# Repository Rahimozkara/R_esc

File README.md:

AM32 Single ESC
⚠️ Disclaimer & Project Status: This is an educational project designed by an engineering student. Please note that the current hardware revision has not yet been physically tested. Manufacture, flash, and use at your own risk.

📖 About the Project
This is an open-source, high-performance single Electronic Speed Controller (ESC) designed for FPV drones and custom robotics. It is fully compatible with the AM32 firmware, providing smooth and efficient brushless DC (BLDC) motor control.

✨ Features
Firmware: AM32 Open Source Firmware

Microcontroller: STM32F051

Estimated Continuous Current: ~20A

Supported Protocols: DShot300 / DShot600 / PWM

Application: FPV Drones & Custom Robotics

🛠️ Hardware Design & Known Issues
The schematic and PCB layout for this project were designed using KiCad. The board layout is optimized for efficient power delivery and stable thermal dissipation.

🛑 Important Hardware Note (Current Sensing):
In the current schematic, an INA199A1DCKR current sense amplifier is used, which features a gain of 50 V/V. However, the default AM32 firmware code expects a current sensor with a gain of 65 V/V.

Recommendation: To ensure accurate current readings, you must either adjust the multiplier in the AM32 firmware code to account for the 50x gain, or replace this IC with a 65x gain variant in future PCB revisions.

🚀 How to Manufacture
All necessary hardware files for manufacturing are included in this repository. You can directly use the provided Gerber files for PCB fabrication.

💻 Flashing & Setup
Initial firmware flashing can be done via the SWD pads located on the board using an ST-Link. Once the bootloader is installed, further firmware updates and configuration can be easily managed via Betaflight passthrough.

📄 License
This project is open-source. Feel free to use, modify, and contribute!

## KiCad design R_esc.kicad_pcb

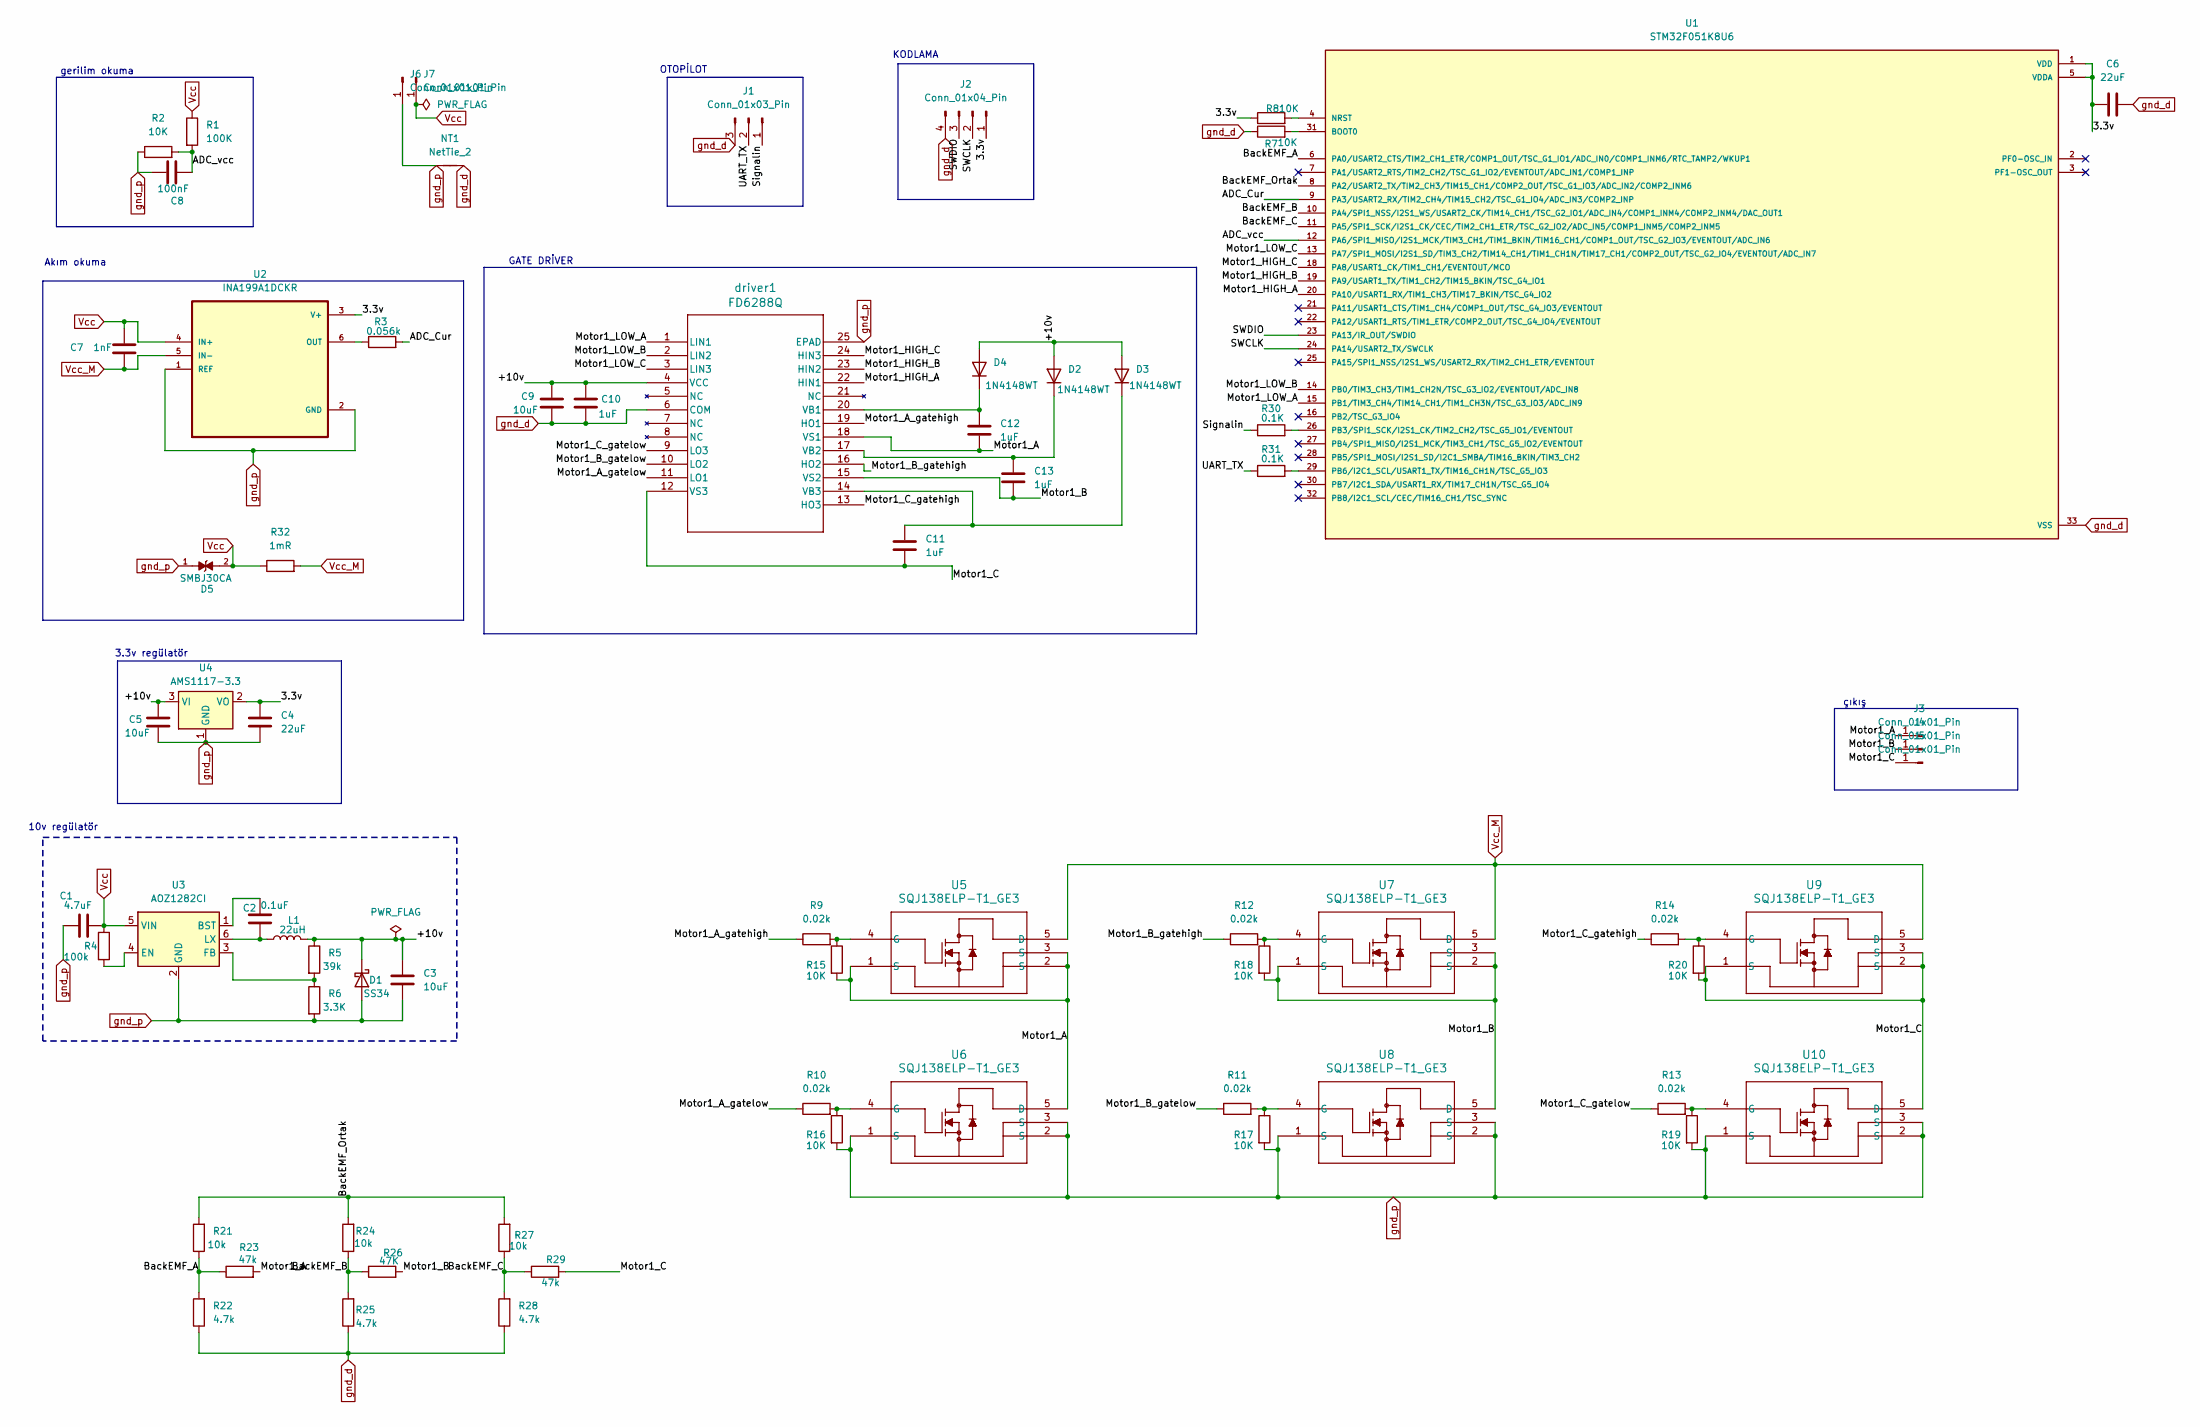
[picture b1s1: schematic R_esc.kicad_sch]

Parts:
C1: 4.7uF; C_0805_2012Metric
C2: 0.1uF; C_0603_1608Metric
C3, C5, C9: 10uF; C_1206_3216Metric
C4, C6: 22uF; C_1206_3216Metric
C7: 1nF; C_0603_1608Metric
C8: 100nF; C_0603_1608Metric
C10, C11, C12, C13: 1uF; C_0805_2012Metric
D1: SS34; D_SMA
D2, D3, D4: 1N4148WT; D_SOD-523
D5: SMBJ30CA; DIOM4336X265N; PARTREV I2102
J1: Conn_01x03_Pin; PinHeader_1x03_P2.54mm_Vertical
J2: Conn_01x04_Pin; PinHeader_1x04_P2.54mm_Vertical
J3, J4, J5, J6, J7: Conn_01x01_Pin; PinHeader_1x01_P2.54mm_Vertical
L1: 22uH; L_6.3x6.3_H3
NT1: NetTie_2; NetTie-2_SMD_Pad0.5mm
R1: 100K; R_0603_1608Metric
R2, R7, R8, R15, R16, R17, R18, R19, R20: 10K; R_0603_1608Metric
R3: 0.056k; R_0603_1608Metric
R4: 100k; R_0603_1608Metric
R5: 39k; R_0603_1608Metric
R6: 3.3K; R_0603_1608Metric
R9, R10, R11, R12, R13, R14: 0.02k; R_0603_1608Metric
R21, R24, R27: 10k; R_0603_1608Metric
R22, R25, R28: 4.7k; R_0603_1608Metric
R23, R29: 47k; R_0603_1608Metric
R26: 47K; R_0603_1608Metric
R30, R31: 0.1K; R_0603_1608Metric
R32: 1mR; R_2512_6332Metric
U1: STM32F051K8U6; QFN50P500X500X60-33N; PARTREV 7
U2: INA199A1DCKR; SOT65P210X110-6N
U3: AOZ1282CI; SOT-23-6
U4: AMS1117-3.3; SOT-223-3_TabPin2
U5, U6, U7, U8, U9, U10: SQJ138ELP-T1_GE3; PowerPAK_SO-8L_3_VIS
driver1: FD6288Q; QFN24_FOR-M

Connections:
/+10v: C3.1, C5.1, C9.1, C10.1, D1.1 (K), D2.2 (A), D3.2 (A), D4.2 (A), L1.2, R5.1, U4.3 (VI), driver1.4 (VCC)
/ADC_Cur: R3.2, U1.9 (PA3/USART2_RX/TIM2_CH4/TIM15_CH2/TSC_G1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)
/ADC_vcc: C8.2, R1.2, R2.2, U1.12 (PA6/SPI1_MISO/I2S1_MCK/TIM3_CH1/TIM1_BK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)
/BackEMF_A: R21.1, R22.2, R23.1, U1.6 (PA0/USART2_CTS/TIM2_CH1_ETR/COMP1_OUT/T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)
/BackEMF_B: R24.1, R25.2, R26.1, U1.10 (PA4/SPI1_NSS/I2S1_WS/USART2_CK/TIM14_CH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)
/BackEMF_C: R27.1, R28.2, R29.1, U1.11 (PA5/SPI1_SCK/I2S1_CK/CEC/TIM2_CH1_ETR/T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)
/BackEMF_Ortak: R21.2, R24.2, R27.2, U1.8 (PA2/USART2_TX/TIM2_CH3/TIM15_CH1/COMP2_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)
/Motor1_A: C12.2, J3.1, R15.2, R23.2, U5.1 (S), U5.2 (S), U5.3 (S), U6.5 (D), driver1.18 (VS1)
/Motor1_A_gatehigh: R9.1, driver1.19 (HO1)
/Motor1_A_gatelow: R10.1, driver1.11 (LO1)
/Motor1_B: C13.2, J4.1, R18.2, R26.2, U7.1 (S), U7.2 (S), U7.3 (S), U8.5 (D), driver1.15 (VS2)
/Motor1_B_gatehigh: R12.1, driver1.16 (HO2)
/Motor1_B_gatelow: R11.1, driver1.10 (LO2)
/Motor1_C: C11.2, J5.1, R20.2, R29.2, U9.1 (S), U9.2 (S), U9.3 (S), U10.5 (D), driver1.12 (VS3)
/Motor1_C_gatehigh: R14.1, driver1.13 (HO3)
/Motor1_C_gatelow: R13.1, driver1.9 (LO3)
/Motor1_HIGH_A: U1.20 (PA10/USART1_RX/TIM1_CH3/TIM17_BKIN/TSC_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), driver1.22 (HIN1)
/Motor1_HIGH_B: U1.19 (PA9/USART1_TX/TIM1_CH2/TIM15_BKIN/TSC_G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), driver1.23 (HIN2)
/Motor1_HIGH_C: U1.18 (PA8/USART1_CK/TIM1_CH1/EVENTOUT/MCO), driver1.24 (HIN3)
/Motor1_LOW_A: U1.15 (PB1/TIM3_CH4/TIM14_CH1/TIM1_CH3N/TSC_G3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), driver1.1 (LIN1)
/Motor1_LOW_B: U1.14 (PB0/TIM3_CH3/TIM1_CH2N/TSC_G3_IO2/EVENT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), driver1.2 (LIN2)
/Motor1_LOW_C: U1.13 (PA7/SPI1_MOSI/I2S1_SD/TIM3_CH2/TIM14_CH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), driver1.3 (LIN3)
/SWCLK: J2.2, U1.24 (PA14/USART2_TX/SWCLK)
/SWDIO: J2.3, U1.23 (PA13/IR_OUT/SWDIO)
/Signalin: J1.1, R30.1
/UART_TX: J1.2, R31.1
unnamed: C13.1, D2.1 (K), driver1.17 (VB2)
unnamed: C11.1, D3.1 (K), driver1.14 (VB3)
unnamed: C12.1, D4.1 (K), driver1.20 (VB1)
unnamed: R7.2, U1.31 (BOOT0)
unnamed: R8.2, U1.4 (NRST)
unnamed: R30.2, U1.26 (PB3/SPI1_SCK/I2S1_CK/TIM2_CH2/TSC_G5_IO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)
unnamed: R31.2, U1.29 (PB6/I2C1_SCL/USART1_TX/TIM16_CH1N/TSC_G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)
unnamed: R3.1, U2.6 (OUT)
unnamed: C2.1, U3.1 (BST)
unnamed: R4.2, U3.4 (EN)
unnamed: R5.2, R6.1, U3.3 (FB)
unnamed: C2.2, L1.1, U3.6 (LX)
unnamed: R9.2, R15.1, U5.4 (G)
unnamed: R10.2, R16.1, U6.4 (G)
unnamed: R12.2, R18.1, U7.4 (G)
unnamed: R11.2, R17.1, U8.4 (G)
unnamed: R14.2, R20.1, U9.4 (G)
unnamed: R13.2, R19.1, U10.4 (G)
VDD: C4.1, C6.2, J2.1, R8.1, U1.1 (VDD), U1.5 (VDDA), U1.17 (VDD), U2.3 (V+), U4.2 (VO)
Vcc: C1.1, C7.2, D5.2, J7.1, R1.1, R4.1, R32.1, U2.4 (IN+), U3.5 (VIN)
Vcc_M: C7.1, R32.2, U2.5 (IN-), U5.5 (D), U7.5 (D), U9.5 (D)
gnd_d: C6.1, C9.2, C10.2, J1.3, J2.4, NT1.2, R7.1, R22.1, R25.1, R28.1, U1.33 (VSS), driver1.6 (COM)
gnd_p: C1.2, C3.2, C4.2, C5.2, C8.1, D1.2 (A), D5.1, J6.1, NT1.1, R2.1, R6.2, R16.2, R17.2, R19.2, U2.1 (REF), U2.2 (GND), U3.2 (GND), U4.1 (GND), U6.1 (S), U6.2 (S), U6.3 (S), U8.1 (S), U8.2 (S), U8.3 (S), U10.1 (S), U10.2 (S), U10.3 (S), driver1.25 (EPAD)

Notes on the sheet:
3.3v regülatör
10v regülatör
KODLAMA
GATE DRİVER
çıkış
gerilim okuma
Akım okuma
OTOPİLOT

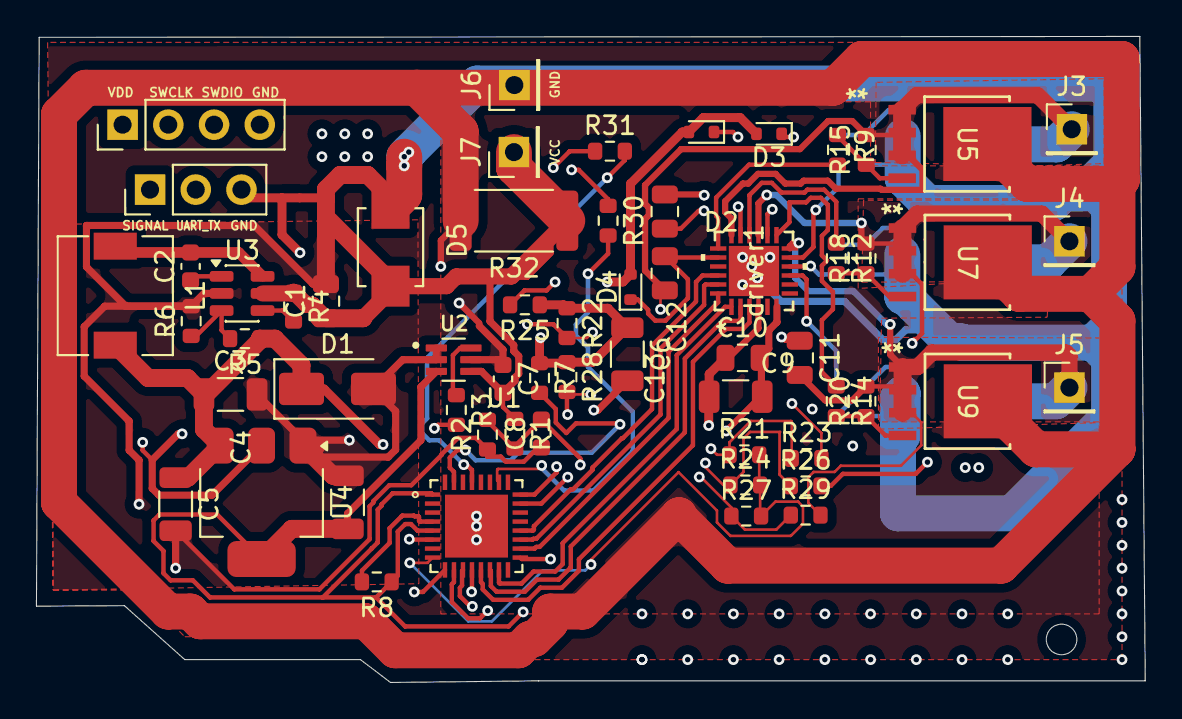
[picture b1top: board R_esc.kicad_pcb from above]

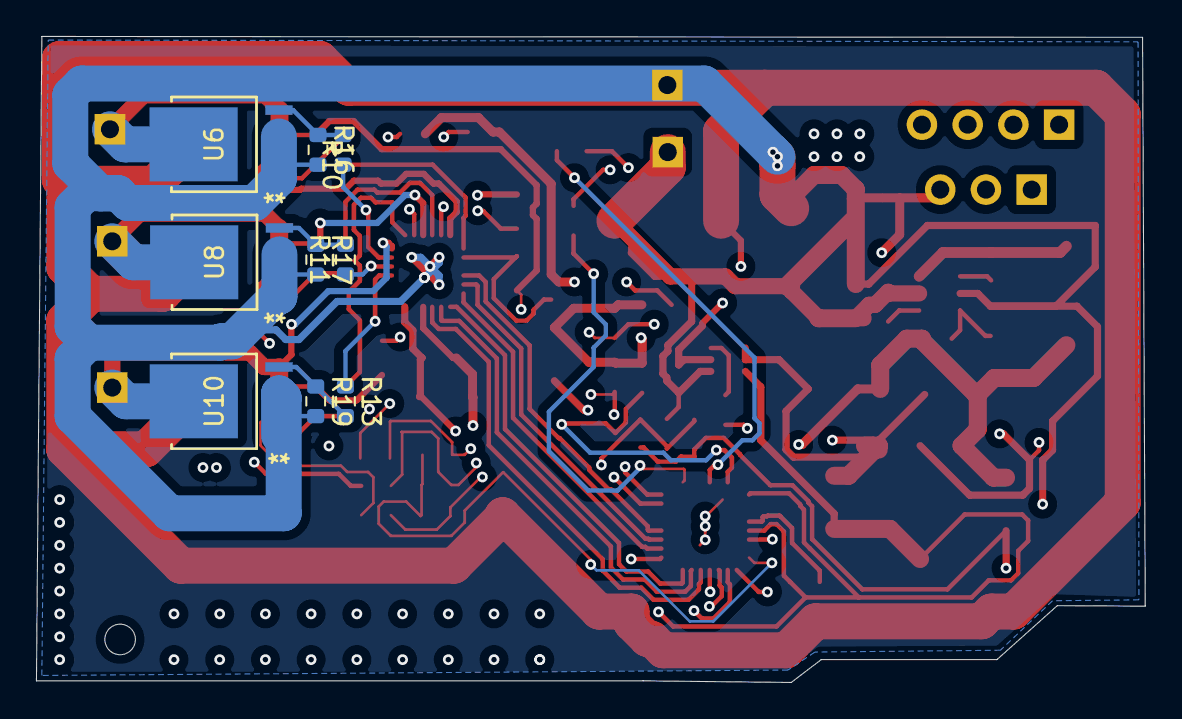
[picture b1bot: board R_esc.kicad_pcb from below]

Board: 4 copper layers, 61.6 x 35.9 mm, 70 parts (9 on the bottom side), 49 nets.

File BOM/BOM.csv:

Reference(s);Quantity;Value / Name;Footprint;Type
U1;1;STM32F051K8U6;QFN50P500X500X60-33N;Microcontroller
driver1;1;FD6288Q;QFN24_FOR-M;Gate Driver
U5, U6, U7, U8, U9, U10;6;SQJ138ELP-T1_GE3;PowerPAK_SO-8L_3_VIS;N-Channel MOSFET
U2;1;INA199A1DCKR;SOT65P210X110-6N;Current Sense Amplifier (Gain: 50)
U3;1;AOZ1282CI;SOT-23-6;Voltage Regulator (Buck)
U4;1;AMS1117-3.3;SOT-223-3_TabPin2;LDO Regulator (3.3V)
D1;"1,""SS34""";D_SMA;Schottky Diode;
D2, D3, D4;3;1N4148WT;D_SOD-523;Signal Diode
D5;"1,""SMBJ30CA""";DIOM4336X265N;TVS Diode;
C4, C6;2;22uF;C_1206_3216Metric;Capacitor
C3, C5, C9;3;10uF;C_1206_3216Metric;Capacitor
C1;1;4.7uF;C_0805_2012Metric;Capacitor
C10, C11, C12, C13;4;1uF;C_0805_2012Metric;Capacitor
C8;1;100nF;C_0603_1608Metric;Capacitor
C2;1;0.1uF;C_0603_1608Metric;Capacitor
C7;1;1nF;C_0603_1608Metric;Capacitor
R1, R4;2;100K;R_0603_1608Metric;Resistor
R23, R26, R29;3;47k;R_0603_1608Metric;Resistor
R5;1;39k;R_0603_1608Metric;Resistor
R2, R7, R8, R15, R16, R17, R18, R19, R20, R21, R24, R27;12;10K;R_0603_1608Metric;Resistor
R22, R25, R28;3;4.7k;R_0603_1608Metric;Resistor
R6;1;3.3K;R_0603_1608Metric;Resistor
R30, R31;2;0.1K;R_0603_1608Metric;Resistor
R3;1;0.056k;R_0603_1608Metric;Resistor
R9, R10, R11, R12, R13, R14;6;0.02k;R_0603_1608Metric;Resistor (Gate)
R32;1;1mR;R_2512_6332Metric;Shunt Resistor
L1;1;22uH;L_6.3x6.3_H3;Inductor
J2;1;Conn_01x04_Pin;PinHeader_1x04_P2.54mm_Vertical;Connector
J1;1;Conn_01x03_Pin;PinHeader_1x03_P2.54mm_Vertical;Connector
J3, J4, J5, J6, J7;5;Conn_01x01_Pin;PinHeader_1x01_P2.54mm_Vertical;Connector (Single Pin)
NT1;1;NetTie_2;NetTie-2_SMD_Pad0.5mm;Net Tie

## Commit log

2026-03-07 ilk commit
2026-03-07 shema and footprints are mostly done
2026-03-09 layout eklendi
2026-03-10 new commit
